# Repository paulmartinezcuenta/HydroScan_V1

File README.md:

<div align="center">

#  Mechatronics & IoT Engineering Projects

*Centralized repository for the development of unified embedded systems.*

</div>

---

> **💡 Manufacturing Note:** To drastically optimize industrial production costs, the PCBs for both projects (HydroScan and AUTOAMBU) have been unified into a single manufacturing panel (Panelized Gerber), sharing the same manufacturing cycle.

---

##  Project 1: HydroScan (Maritime IoT Node)
**Smart buoy for real-time water quality monitoring.***

* 📡 **Telemetry:** Real-time environmental data transmission via LTE networks.
* 📍 **Tracking:** Integrated GPS geolocation for precise positioning of the node.
* 🔋 **Power:** Self-sustaining energy system utilizing solar panels to charge and monitor the sensors autonomously.
* 🔬 **Application:** Oceanographic research and environmental monitoring in coastal areas.
* 📁 [**Explore HydroScan Firmware ➔**](./Firmware_HydroScan)

---

## 🫁 Project 2: AUTOAMBU (Automated Respirator)
**Automated respiratory assistance system.**

* ⚙️ **Actuation & Control:** Precision mechanical control using a DC motor equipped with an encoder and driven by an L298N H-bridge.
* ⚡ **Power Management:** USB Super Fast Charging architecture designed to simultaneously power the circuitry and charge the system.
* 🧠 **Architecture:** Centralized ESP32 32U control logic with dedicated thermal management for continuous and safe operation.
* 📁 [**Explore AUTOAMBU Firmware ➔**](./Firmware_AUTOAMBU)

---

## 👥 Development Team

* ⚡ **Paul** - Hardware Design and PCB Routing 
* 🏗️ **Miguel** - Structural 3D Design
* 💻 **Isaias** - Firmware Development
* 💻 **Alberto** - Firmware Development

---

## 📂 Repository Architecture

| Directory | Description |
| :--- | :--- |
| 🖨️ [**`Hardware_Panelized/`**](./Hardware_Panelized) | Unified KiCad project and joint production Gerber files ready for manufacturing. |
| 💻 [**`Firmware_AUTOAMBU/`**](./Firmware_AUTOAMBU) | Source code (C/C++) and control routines for the medical respirator. |
| 📡 [**`Firmware_HydroScan/`**](./Firmware_HydroScan) | Telemetry logic and sensor reading for the maritime buoy. |
| 📚 [**`Docs/`**](./Docs) | Technical documentation, datasheets, schematics, and 3D models for both systems. |

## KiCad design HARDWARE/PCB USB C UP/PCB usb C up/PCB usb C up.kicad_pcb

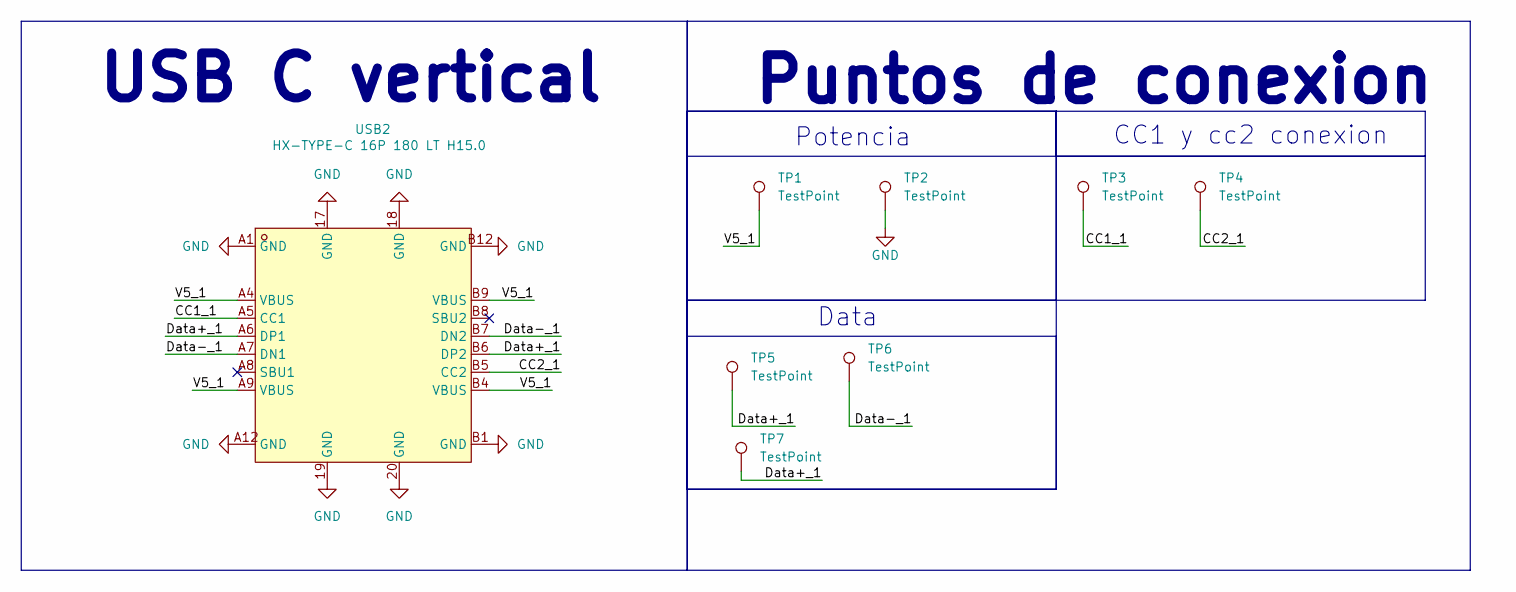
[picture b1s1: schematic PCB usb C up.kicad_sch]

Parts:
TP1, TP2, TP3, TP4, TP5, TP6, TP7: TestPoint; TestPoint_THTPad_2.0x2.0mm_Drill1.0mm
USB2: HX-TYPE-C 16P 180 LT H15.0; USB-C-SMD_HX-TYPE-C-16P-180-LT-H15.0; LCSC Part C49261573

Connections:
/CC1_1: TP3.1 (1_1), USB2.A5 (CC1)
/CC2_1: TP4.1 (1_1), USB2.B5 (CC2)
/Data+_1: TP5.1 (1_1), TP7.1 (1_1), USB2.A6 (DP1), USB2.B6 (DP2)
/Data-_1: TP6.1 (1_1), USB2.A7 (DN1), USB2.B7 (DN2)
/V5_1: TP1.1 (1_1), USB2.A4 (VBUS), USB2.A9 (VBUS), USB2.B4 (VBUS), USB2.B9 (VBUS)
GND: TP2.1 (1_1), USB2.17 (GND), USB2.18 (GND), USB2.19 (GND), USB2.20 (GND), USB2.A1 (GND), USB2.A12 (GND), USB2.B1 (GND), USB2.B12 (GND)

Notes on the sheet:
Potencia
USB C vertical
Data
CC1 y cc2 conexion
Puntos de conexion

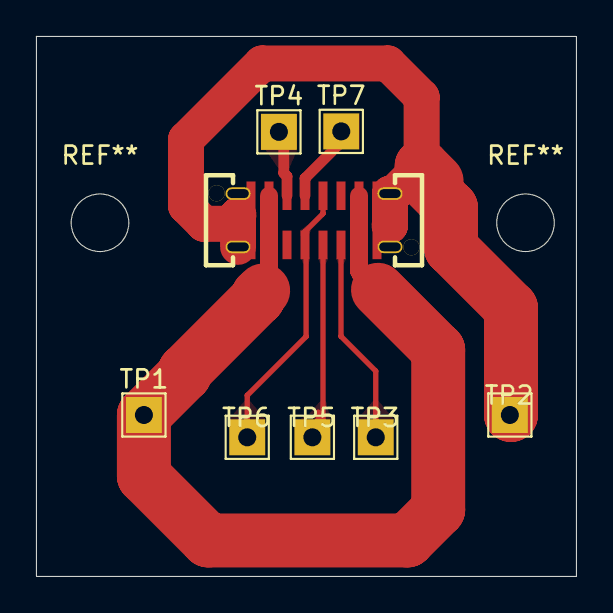
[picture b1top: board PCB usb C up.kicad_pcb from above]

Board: 2 copper layers, 30.0 x 30.0 mm, 8 parts (0 on the bottom side), 6 nets.

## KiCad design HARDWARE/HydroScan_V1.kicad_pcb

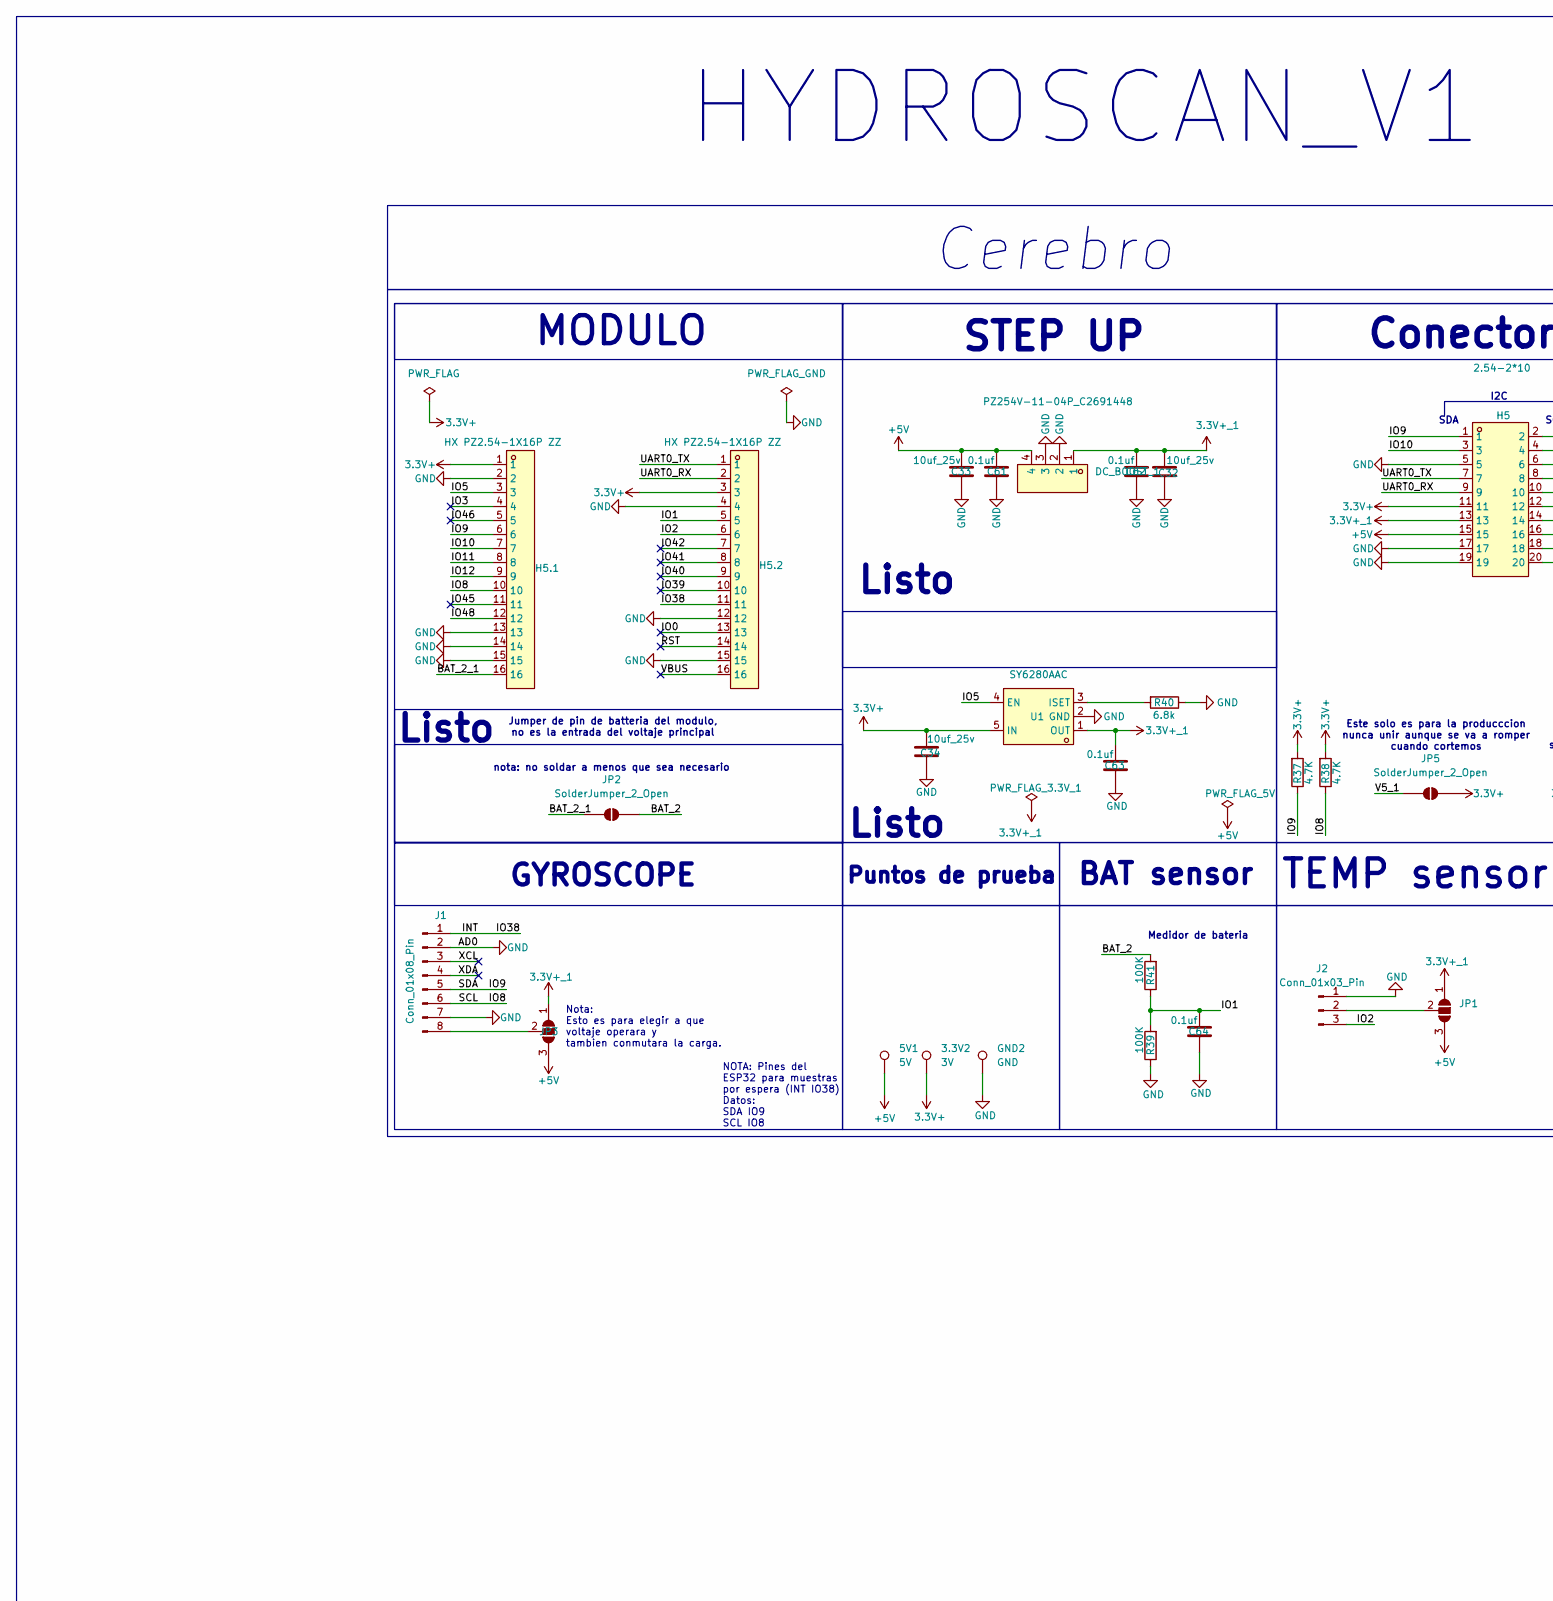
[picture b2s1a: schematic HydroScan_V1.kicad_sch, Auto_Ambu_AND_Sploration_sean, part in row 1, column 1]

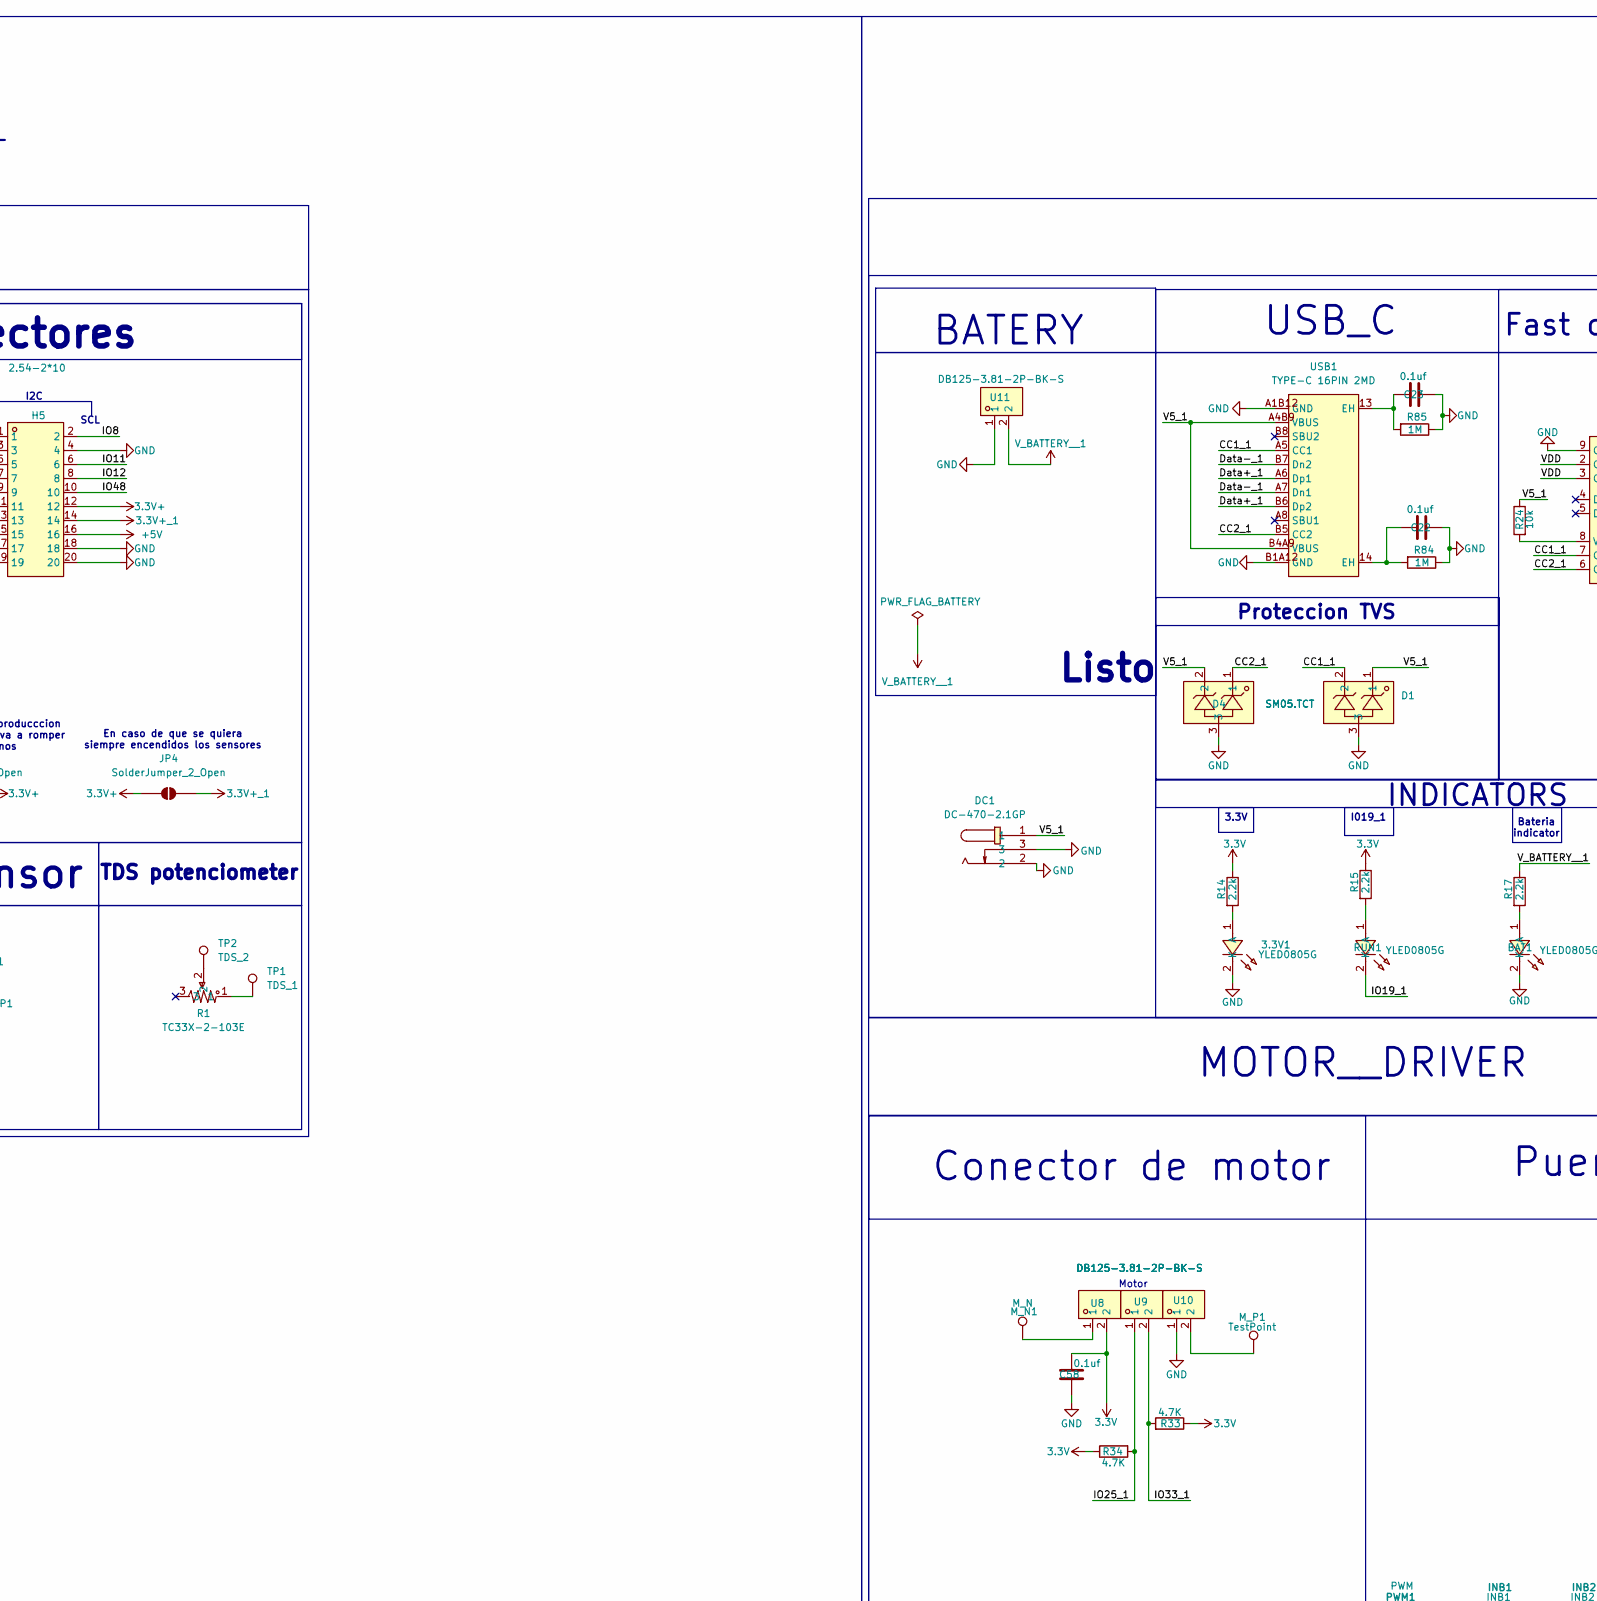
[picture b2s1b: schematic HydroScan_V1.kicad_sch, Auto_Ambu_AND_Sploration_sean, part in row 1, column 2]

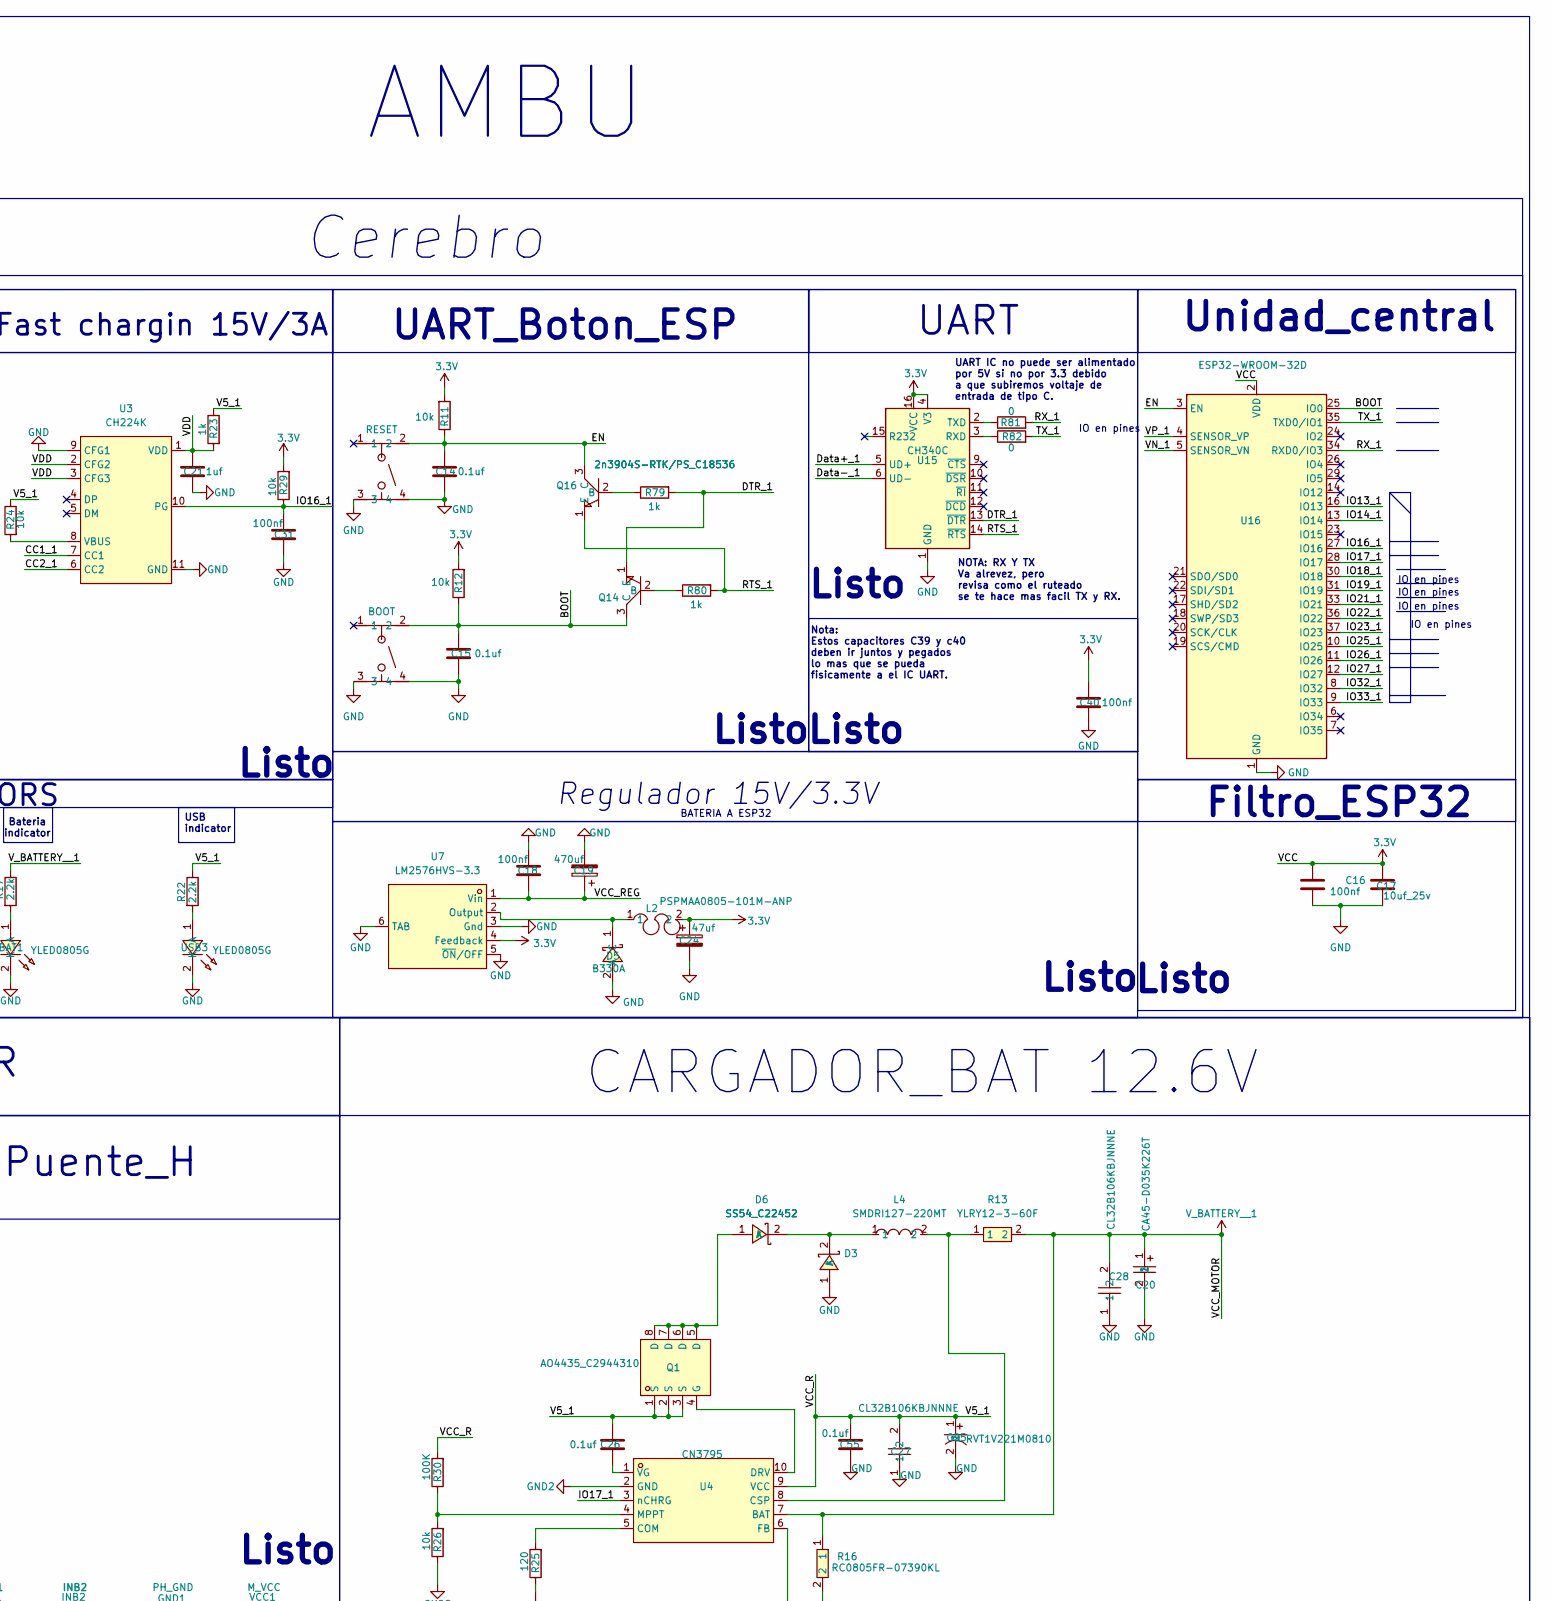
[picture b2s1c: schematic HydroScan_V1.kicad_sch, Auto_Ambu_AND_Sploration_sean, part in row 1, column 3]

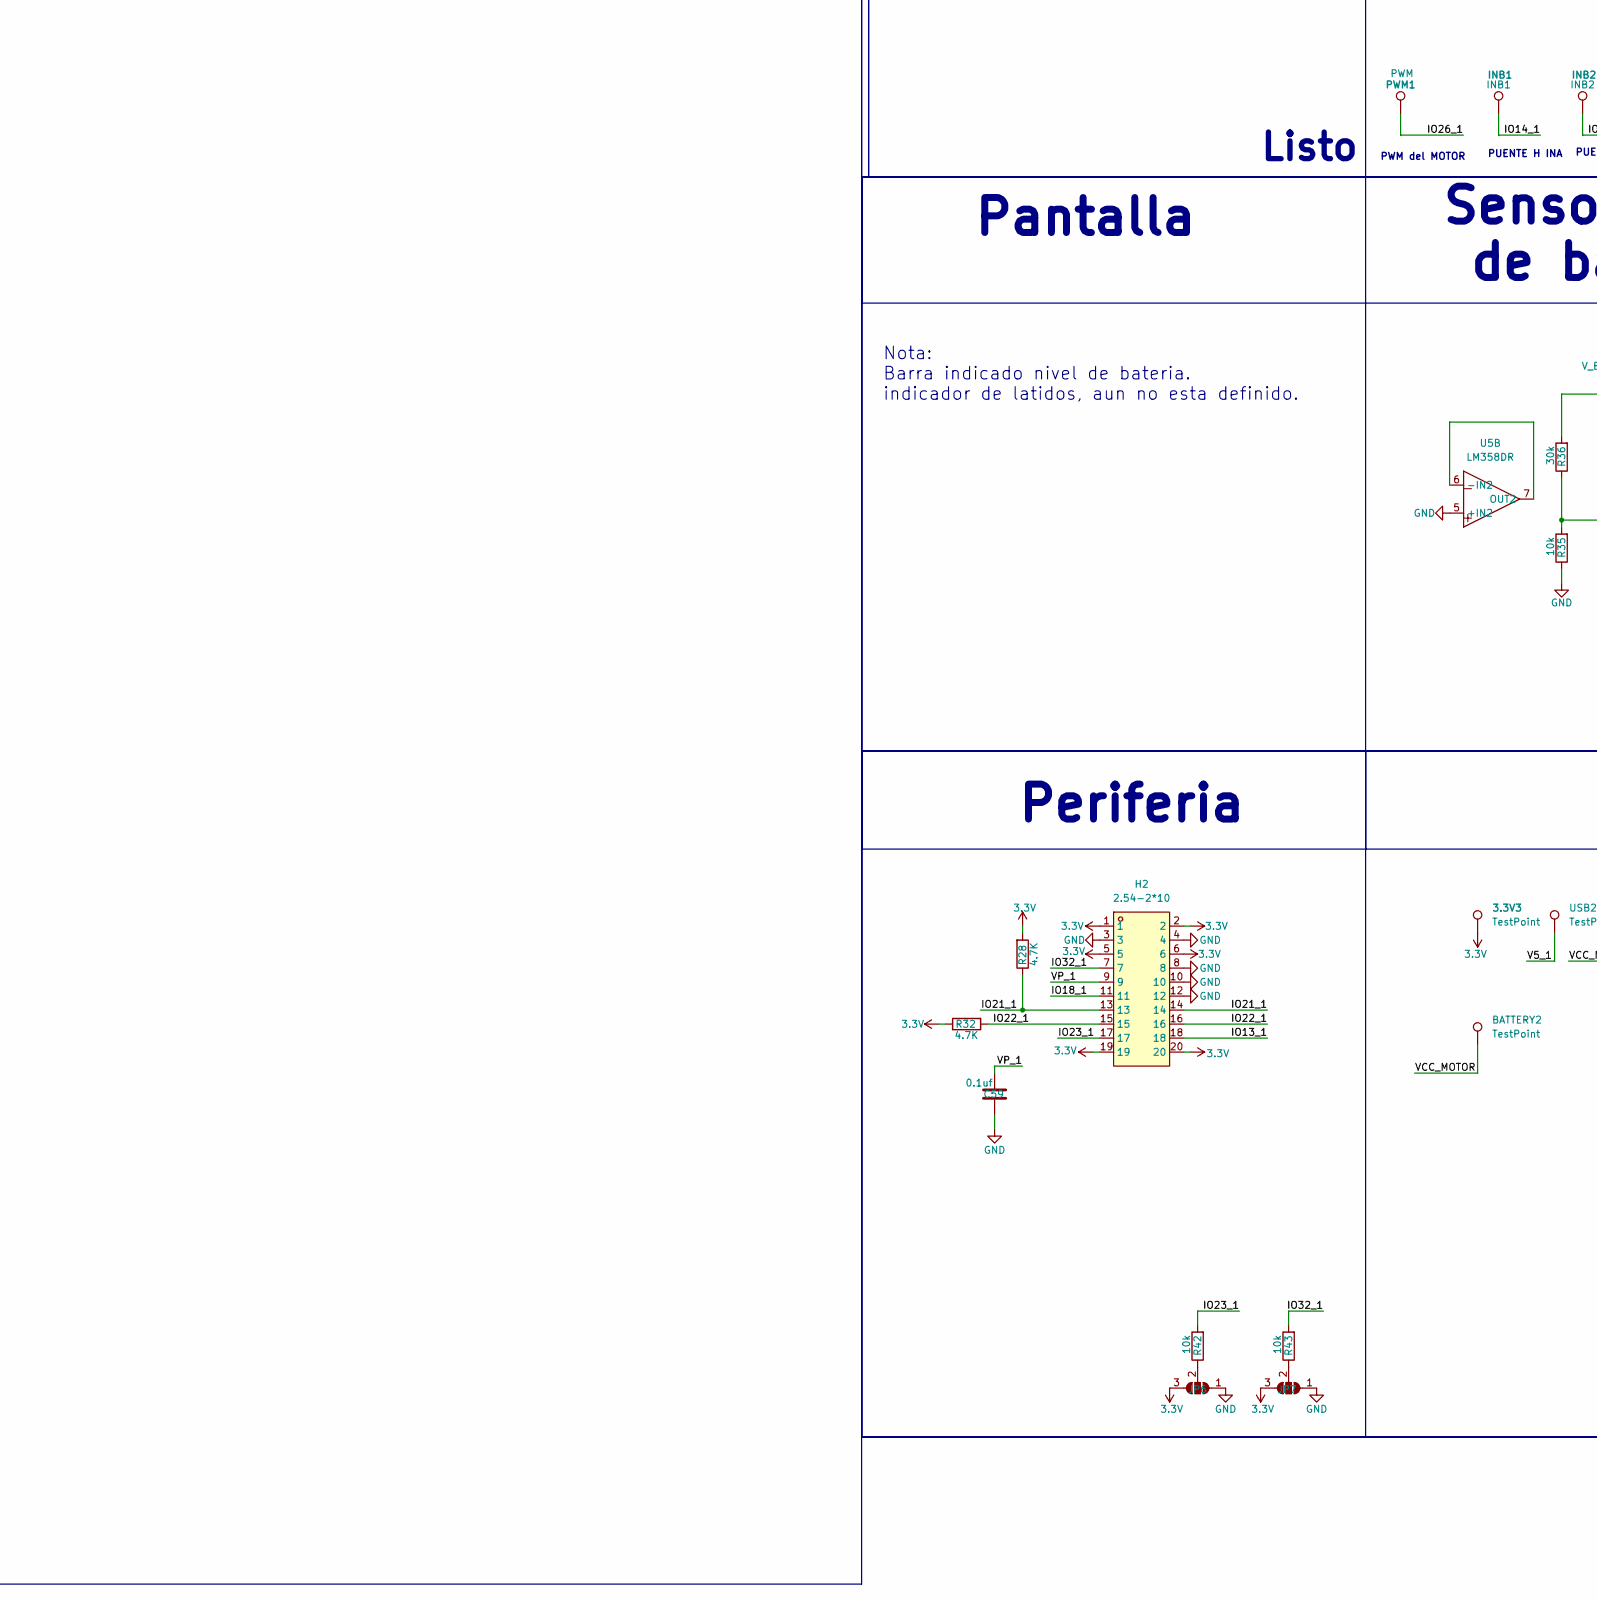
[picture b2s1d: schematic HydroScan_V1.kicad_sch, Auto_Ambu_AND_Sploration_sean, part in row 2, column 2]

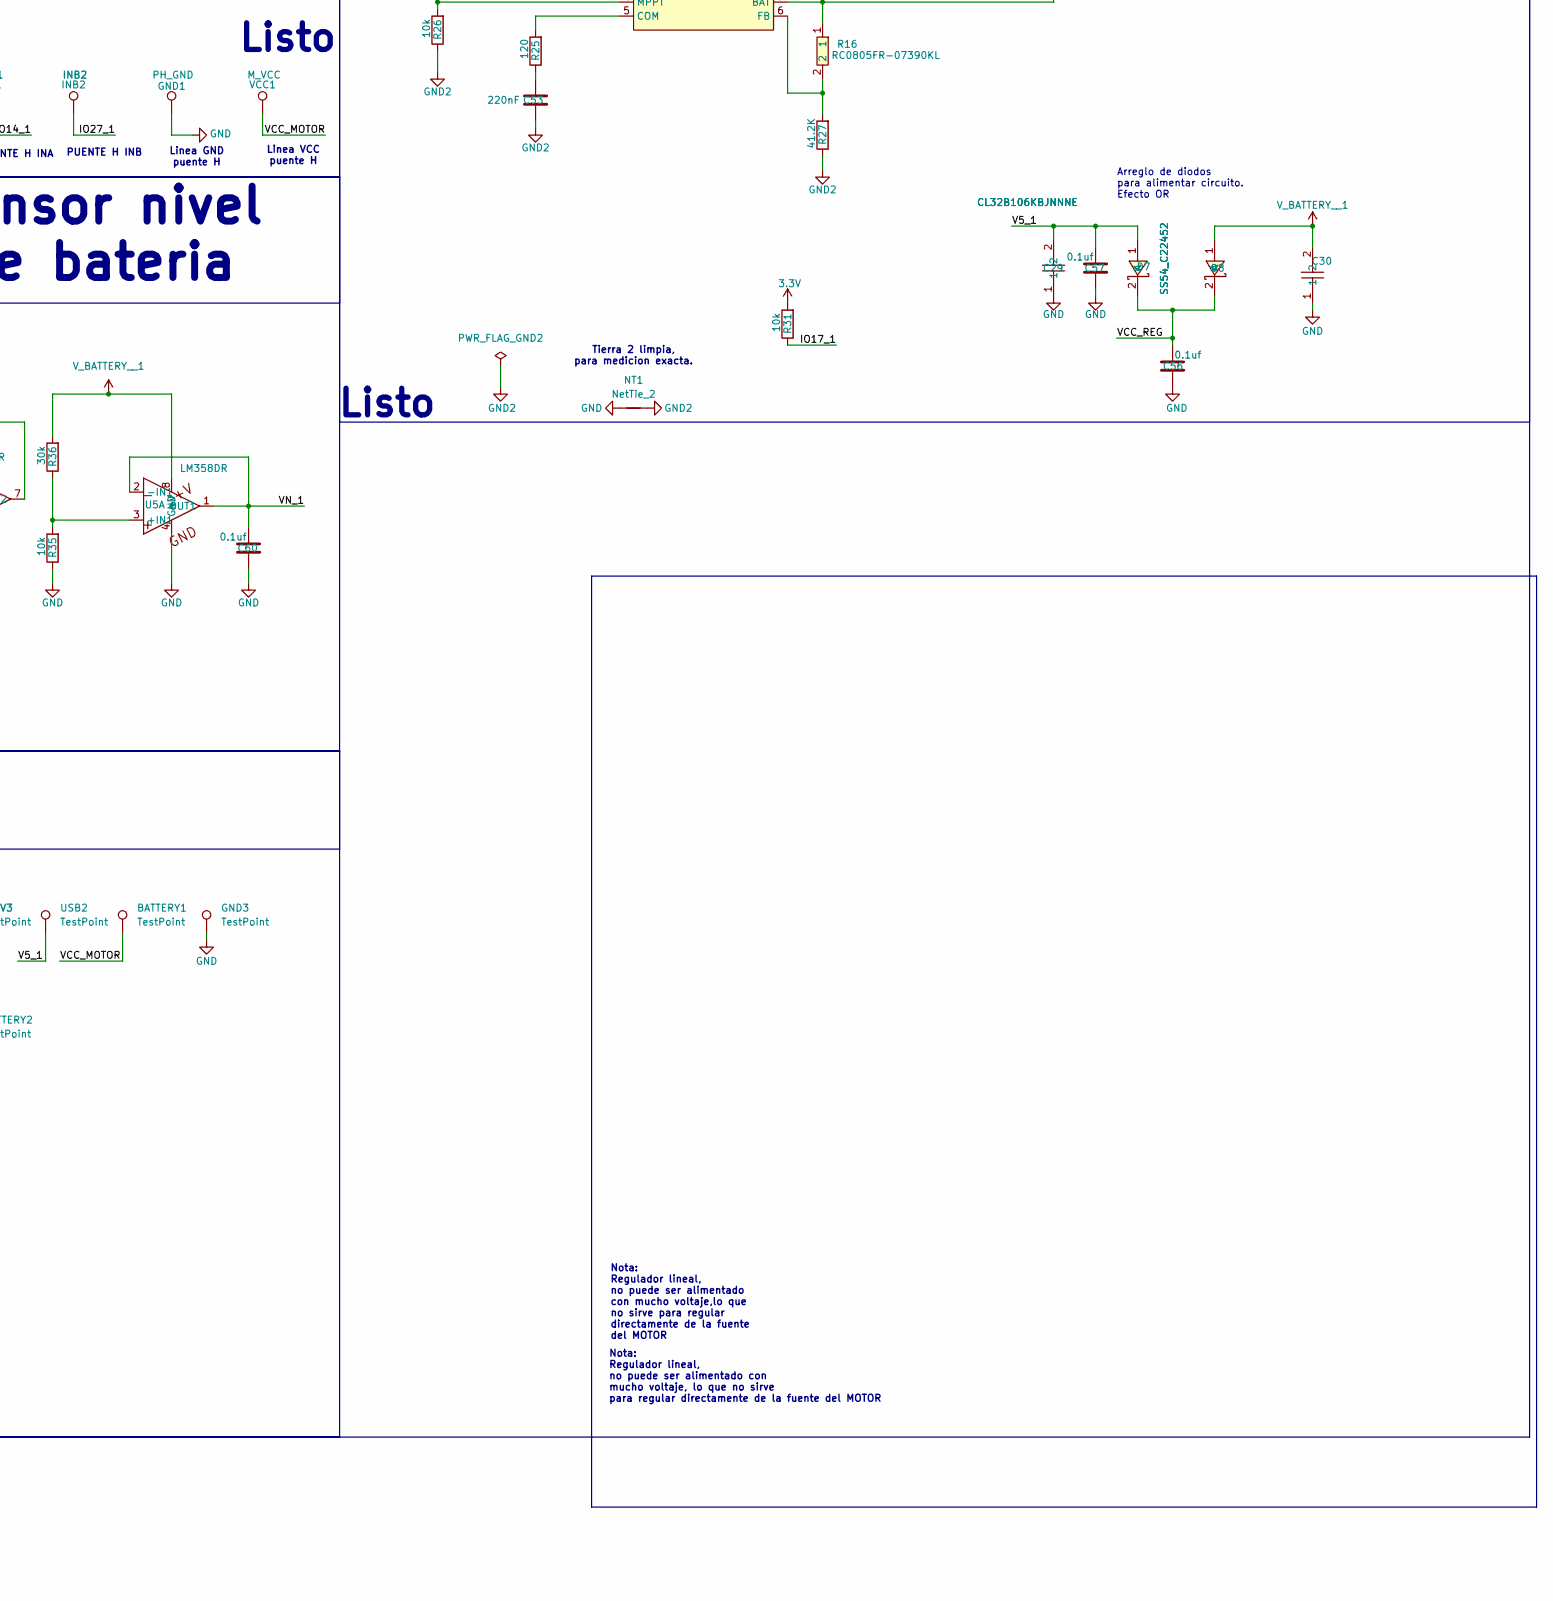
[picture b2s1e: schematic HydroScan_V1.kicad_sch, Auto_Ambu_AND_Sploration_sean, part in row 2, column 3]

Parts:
3.3V1: YLED0805G; LED0805-FD-GREEN; MPN YLED0805G; LCSC Part C25170728
3.3V2: 3V; TestPoint_Pad_2.5x2.5mm
3.3V3: TestPoint; TestPoint_Pad_2.0x2.0mm
5V1: 5V; TestPoint_Pad_2.5x2.5mm
BAT1: YLED0805G; LED0805-FD-GREEN; MPN YLED0805G; LCSC Part C25170728
BATTERY1, BATTERY2: TestPoint; TestPoint_Pad_2.0x2.0mm
C14, C15, C22, C23, C26, C55, C56, C57, C58, C59, C60, C61, C62, C63, C64: 0.1uf; C_0805_2012Metric_Pad1.18x1.45mm_HandSolder
C16, C18, C31, C40: 100nf; C_0805_2012Metric_Pad1.18x1.45mm_HandSolder
C17, C32, C33, C34: 10uf_25v; C_0805_2012Metric_Pad1.18x1.45mm_HandSolder
C19: 470uf; C_Elec_10x10.2; LCSC C72518
C20: CA45-D035K226T; CAP-SMD_L7.3-W4.3-R-RD; MPN CA45-D035K226T; LCSC Part C126947
C21: 1uf; C_0805_2012Metric_Pad1.18x1.45mm_HandSolder
C24: 47uf; C_Elec_6.3x7.7; LCSC C72523
C25: RVT1V221M0810; CAP-SMD_BD8.0-L8.3-W8.3-LS9.1-FD; MPN RVT1V221M0810; LCSC Part C3340
C27, C28, C29, C30: CL32B106KBJNNNE; C1210; MPN CL32B106KBJNNNE; LCSC Part C138687
C53: 220nF; C_0805_2012Metric_Pad1.18x1.45mm_HandSolder
D1, D4: SM05.TCT; SOT-23-3_L2.9-W1.3-P0.95-LS2.4-BR; MPN SM05.TCT; LCSC Part C85197
D3, D6, D7, D8: SS54_C22452; SMA_L4.4-W2.8-LS5.4-R-RD; MPN SS54; LCSC Part C22452
D5: B330A; SMA_L4.3-W2.6-LS5.1-RD; MPN B330A; LCSC Part C52037930
DC1: DC-470-2.1GP; DC-IN-TH_DC-470-2.1GP; MPN DC-470-2.1GP; LCSC Part C194407
DC_BOOST_1: PZ254V-11-04P_C2691448; HDR-TH_4P-P2.54-V-M; MPN PZ254V-11-04P; LCSC Part C2691448
GND1: PH_GND; PinHeader_1x01_P2.00mm_Vertical
GND2: GND; TestPoint_Pad_2.5x2.5mm
GND3: TestPoint; TestPoint_Pad_2.0x2.0mm
H2, H5: 2.54-2*10; HDR-TH_20P-P2.54-V-M-R2-C10-S2.54; MPN 2.54-2*10; LCSC Part C5116480
H5.1, H5.2: HX PZ2.54-1X16P ZZ; HDR-TH_16P-P2.54-V-M_2; MPN HX PZ2.54-1x16P ZZ; LCSC Part C42372508
INB1: INB1; PinHeader_1x01_P2.00mm_Vertical
INB2: INB2; PinHeader_1x01_P2.00mm_Vertical
J1: Conn_01x08_Pin; MPU6050_Module
J2: Conn_01x03_Pin; PinHeader_1x03_P2.54mm_Vertical
JP1, JP3, JP6, JP7: SolderJumper_3_Open; SolderJumper-3_P1.3mm_Open_RoundedPad1.0x1.5mm_NumberLabels
JP2, JP4, JP5: SolderJumper_2_Open; SolderJumper-2_P1.3mm_Open_Pad1.0x1.5mm
L2: PSPMAA0805-101M-ANP; IND-SMD_L8.5-W8.0_PCC-M0854M; LCSC Part C2962892
L4: SMDRI127-220MT; IND-SMD_L12.3-W12.3_SMDRI127; MPN SMDRI127-220MT; LCSC Part C9905
M_N1: M_N; PinHeader_1x01_P2.00mm_Vertical
M_P1: TestPoint; PinHeader_1x01_P2.00mm_Vertical
NT1: NetTie_2; NetTie-2_SMD_Pad0.5mm
PWM1: PWM; PinHeader_1x01_P2.00mm_Vertical
Q1: AO4435_C2944310; SOP-8_L5.0-W3.8-P1.27-LS6.0-BL; MPN AO4435; LCSC Part C2944310
Q14, Q16: 2n3904S-RTK/PS_C18536; SOT-23-3_L2.9-W1.3-P1.90-LS2.4-TR; LCSC Part C18536
R1: TC33X-2-103E; RES-ADJ-SMD_3P-L3.0-W3.8-P1.75-BR; MPN TC33X-2-103E; LCSC Part C719176
R11, R12, R26, R29, R31, R35, R42, R43: 10k; R_0805_2012Metric_Pad1.20x1.40mm_HandSolder
R13: YLRY12-3-60F; R2512; MPN YLRY12-3-60F; LCSC Part C22468068
R14, R15, R17, R22: 2.2k; R_0805_2012Metric_Pad1.20x1.40mm_HandSolder
R16: RC0805FR-07390KL; R0805; MPN RC0805FR-07390KL; LCSC Part C137535
R23, R79, R80: 1k; R_0805_2012Metric_Pad1.20x1.40mm_HandSolder
R24: 10k; C_0805_2012Metric_Pad1.18x1.45mm_HandSolder
R25: 120; R_0805_2012Metric_Pad1.20x1.40mm_HandSolder
R27: 41.2K; R_0805_2012Metric_Pad1.20x1.40mm_HandSolder; LCSC C2077335
R28, R32, R33, R34, R37, R38: 4.7K; R_0805_2012Metric_Pad1.20x1.40mm_HandSolder
R30, R39, R41: 100K; R_0805_2012Metric_Pad1.20x1.40mm_HandSolder
R36: 30k; R_0805_2012Metric_Pad1.20x1.40mm_HandSolder
R40: 6.8k; R_0805_2012Metric_Pad1.20x1.40mm_HandSolder
R81, R82: 0; R_0805_2012Metric_Pad1.20x1.40mm_HandSolder
R84, R85: 1M; R_0805_2012Metric_Pad1.20x1.40mm_HandSolder
RUN1: YLED0805G; LED0805-FD-GREEN; MPN YLED0805G; LCSC Part C25170728
SW2: BOOT; SW-SMD_4P-L6.0-W6.0-P4.50-LS8.2; LCSC Part C7528752
SW4: RESET; SW-SMD_4P-L6.0-W6.0-P4.50-LS8.2; LCSC Part C7528752
TP1: TDS_1; TestPoint_THTPad_D4.0mm_Drill2.0mm
TP2: TDS_2; TestPoint_THTPad_D4.0mm_Drill2.0mm
U1: SY6280AAC; SOT-23-5_L3.0-W1.7-P0.95-LS2.8-BL; MPN SY6280AAC; LCSC Part C55136
U3: CH224K; ESSOP-10_L4.9-W3.9-P1.0-LS6.0-TL-EP; MPN CH224K; LCSC Part C970725
U4: CN3795; SSOP-10_L4.9-W3.9-P1.00-LS6.0-BL; MPN CN3795; LCSC Part C150555
U5: LM358DR; SOIC-8_L5.0-W4.0-P1.27-LS6.0-BL; MPN LM358DR; LCSC Part C5423
U7: LM2576HVS-3.3; PG-TO-263-5_L10.2-W8.7-P1.70-LS14.4-BR; LCSC Part C347436
U8, U9, U10, U11: DB125-3.81-2P-BK-S; CONN-TH_2P-P3.81_DB125-3.81-2P-BK-S; MPN DB125-3.81-2P-BK-S; LCSC Part C430618
U15: CH340C; SOIC-16_3.9x9.9mm_P1.27mm
U16: ESP32-WROOM-32D; ESP32-WROOM-32U
USB1: TYPE-C 16PIN 2MD; USB-C-SMD_TYPE-C-16PIN-2MD-073; MPN TYPE-C 16PIN 2MD(073); LCSC Part C2765186
USB2: TestPoint; TestPoint_Pad_2.0x2.0mm
USB3: YLED0805G; LED0805-FD-GREEN; MPN YLED0805G; LCSC Part C25170728
VCC1: M_VCC; PinHeader_1x01_P2.00mm_Vertical

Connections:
3.3V: 3.3V3.1 (1_1), C16.1, C17.1, C24.1, C40.1, C58.2, H2.1, H2.2, H2.5, H2.6, H2.19, H2.20, JP6.3 (B), JP7.3 (B), L2.2, R11.2, R12.2, R14.1, R15.1, R28.2, R29.2, R31.2, R32.1, R33.1, R34.1, U7.4 (Feedback), U8.2, U15.4 (V3), U15.16 (VCC), U16.2 (VDD)
3.3V+: 3.3V2.1 (1_1), C34.1, H5.11, H5.12, H5.1.1, H5.2.3, JP4.1 (A), JP5.2 (B), R37.2, R38.2, U1.5 (IN)
3.3V+_1: C32.1, C62.2, C63.2, DC_BOOST_1.1, H5.13, H5.14, JP1.1 (A), JP3.1 (A), JP4.2 (B), U1.1 (OUT)
+5V: 5V1.1 (1_1), C33.1, C61.2, DC_BOOST_1.4, H5.15, H5.16, JP1.3 (B), JP3.3 (B)
/BAT_2: JP2.2 (B), R41.2
/BAT_2_1: H5.1.16, JP2.1 (A)
/BOOT: C15.1, Q14.3 (C), R12.1, SW2.2, U16.25 (IO0)
/CC1_1: D1.2, U3.7 (CC1), USB1.A5 (CC1)
/CC2_1: D4.1, U3.6 (CC2), USB1.B5 (CC2)
/DTR_1: Q14.1 (E), R79.2, U15.13 (~DTR)
/Data+_1: U15.5 (UD+), USB1.A6 (Dp1), USB1.B6 (Dp2)
/Data-_1: U15.6 (UD-), USB1.A7 (Dn1), USB1.B7 (Dn2)
/EN: C14.1, Q16.3 (C), R11.1, SW4.2, U16.3 (EN)
/INT: H5.2.11, J1.1
/IO0: H5.2.13
/IO1: C64.2, H5.2.5, R39.2, R41.1
/IO2: H5.2.6, J2.3
/IO3: H5.1.4
/IO5: H5.1.3, U1.4 (EN)
/IO8: H5.2, H5.1.10, J1.6, R38.1
/IO9: H5.1, H5.1.6, J1.5, R37.1
/IO10: H5.3, H5.1.7
/IO11: H5.6, H5.1.8
/IO12: H5.8, H5.1.9
/IO13_1: H2.18, U16.16 (IO13)
/IO14_1: INB1.1 (1_1), U16.13 (IO14)
/IO16_1: C31.2, R29.1, U3.10 (PG), U16.27 (IO16)
/IO17_1: R31.1, U4.3 (nCHRG), U16.28 (IO17)
/IO18_1: H2.11, U16.30 (IO18)
/IO19_1: RUN1.2 (K), U16.31 (IO19)
/IO21_1: H2.13, H2.14, R28.1, U16.33 (IO21)
/IO22_1: H2.15, H2.16, R32.2, U16.36 (IO22)
/IO23_1: H2.17, R42.2, U16.37 (IO23)
/IO25_1: R34.2, U9.1, U16.10 (IO25)
/IO26_1: PWM1.1 (1_1), U16.11 (IO26)
/IO27_1: INB2.1 (1_1), U16.12 (IO27)
/IO32_1: H2.7, R43.2, U16.8 (IO32)
/IO33_1: R33.2, U9.2, U16.9 (IO33)
/IO39: H5.2.10
/IO40: H5.2.9
/IO41: H5.2.8
/IO42: H5.2.7
/IO45: H5.1.11
/IO46: H5.1.5
/IO48: H5.10, H5.1.12
/RST: H5.2.14
/RTS_1: Q16.1 (E), R80.2, U15.14 (~RTS)
/RX_1: R81.2, U16.34 (RXD0/IO3)
/TX_1: R82.2, U16.35 (TXD0/IO1)
/UART0_RX: H5.9, H5.2.2
/UART0_TX: H5.7, H5.2.1
/V5_1: C25.1, C26.2, C27.2, C29.2, C55.2, C57.2, D1.1, D4.2, D7.1 (A), DC1.1, JP5.1 (A), Q1.1 (S), Q1.2 (S), Q1.3 (S), R22.1, R23.1, R24.1, R30.2, U4.9 (VCC), USB1.A4B9 (VBUS), USB1.B4A9 (VBUS), USB2.1 (1_1)
/VBUS: H5.2.16
/VCC_REG: C18.1, C19.1, C56.2, D7.2 (K), D8.2 (K), U7.1 (Vin)
/VDD: C21.1, R23.2, U3.1 (VDD), U3.2 (CFG2), U3.3 (CFG3)
/VN_1: C60.2, U5.1 (OUT1), U5.2 (-IN1), U16.5 (SENSOR_VN)
/VP_1: C59.2, H2.9, U16.4 (SENSOR_VP)
/XCL: J1.3
/XDA: J1.4
GND: 3.3V1.2 (K), BAT1.2 (K), C14.2, C15.2, C16.2, C17.2, C18.2, C19.2, C20.2, C21.2, C22.2, C23.2, C24.2, C25.2, C27.1, C28.1, C29.1, C30.1, C31.1, C32.2, C33.2, C34.2, C40.2, C55.1, C56.1, C57.1, C58.1, C59.1, C60.1, C61.1, C62.1, C63.1, C64.1, D1.3, D3.1 (A), D4.3, D5.2 (A), DC1.2, DC1.3, DC_BOOST_1.2, DC_BOOST_1.3, GND1.1 (1_1), GND2.1 (1_1), GND3.1 (1_1), H2.3, H2.4, H2.8, H2.10, H2.12, H5.4, H5.5, H5.17, H5.18, H5.19, H5.20, H5.1.2, H5.1.13, H5.1.14, H5.1.15, H5.2.4, H5.2.12, H5.2.15, J1.2, J1.7, J2.1, JP6.1 (A), JP7.1 (A), NT1.1, R35.1, R39.1, R40.1, R84.1, R85.1, SW2.3, SW2.4, SW4.3, SW4.4, U1.2 (GND), U3.9 (CFG1), U3.11 (GND), U5.4 (GND), U5.5 (+IN2), U7.3 (Gnd), U7.5 (~ON/OFF), U7.6 (TAB), U10.1, U11.1, U15.1 (GND), U16.1 (GND), U16.15 (GND), U16.38 (GND), U16.39 (GND), USB1.A1B12 (GND), USB1.B1A12 (GND), USB3.2 (K); also elsewhere on the board
GND2: C53.1, NT1.2, R26.1, R27.1, U4.2 (GND)
unnamed: 3.3V1.1 (A), R14.2
unnamed: BAT1.1 (A), R17.2
unnamed: C22.1, R84.2, USB1.14 (EH)
unnamed: C23.1, R85.2, USB1.13 (EH)
unnamed: C53.2, R25.1
unnamed: D3.2 (K), D6.2 (K), L4.1
unnamed: D5.1 (C), L2.1, U7.2 (Output)
unnamed: D6.1 (A), Q1.5 (D), Q1.6 (D), Q1.7 (D), Q1.8 (D)
unnamed: J1.8, JP3.2 (C)
unnamed: J2.2, JP1.2 (C)
unnamed: JP6.2 (C), R42.1
unnamed: JP7.2 (C), R43.1
unnamed: M_N1.1 (1_1), U8.1
unnamed: M_P1.1 (1_1), U10.2
unnamed: Q1.4 (G), U4.10 (DRV)
unnamed: Q14.2 (B), R80.1
unnamed: Q16.2 (B), R79.1
unnamed: R1.1, TP1.1 (1_1)
unnamed: R1.2, TP2.1 (1_1)
unnamed: R15.2, RUN1.1 (A)
unnamed: R40.2, U1.3 (ISET)
unnamed: R24.2, U3.8 (VBUS)
unnamed: R25.2, U4.5 (COM)
unnamed: L4.2, R13.1, U4.8 (CSP)
unnamed: R16.2, R27.2, U4.6 (FB)
unnamed: R26.2, R30.1, U4.4 (MPPT)
unnamed: C26.1, U4.1 (VG)
unnamed: R35.2, R36.1, U5.3 (+IN1)
unnamed: U5.6 (-IN2), U5.7 (OUT2)
unnamed: R82.1, U15.3 (RXD)
unnamed: R81.1, U15.2 (TXD)
unnamed: R22.2, USB3.1 (A)
V_BATTERY__1: BATTERY1.1 (1_1), BATTERY2.1 (1_1), C20.1, C28.2, C30.2, D8.1 (A), R13.2, R16.1, R17.1, R36.2, U4.7 (BAT), U5.8 (+V), U11.2, VCC1.1 (1_1)

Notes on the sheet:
Periferia
MOTOR__DRIVER
NOTA: RX Y TX Va alrevez, pero revisa como el ruteado se te hace mas facil TX y RX.
IO en pines
Jumper de pin de batteria del modulo, no es la entrada del voltaje principal
Unidad_central
BATERY
Nota: Esto es para elegir a que voltaje operara y tambien conmutara la carga.
NOTA: Pines del ESP32 para muestras por espera (INT IO38) Datos: SDA IO9 SCL IO8
HYDROSCAN_V1
Linea GND puente H
Este solo es para la producccion nunca unir aunque se va a romper cuando cortemos
Nota: Regulador lineal, no puede ser alimentado con mucho voltaje, lo que no sirve para regular directamente de la fuente del MOTOR
Listo
Linea VCC puente H
Nota: Barra indicado nivel de bateria. indicador de latidos, aun no esta definido.
SCL
PWM del MOTOR
UART
Nota: Estos capacitores C39 y c40 deben ir juntos y pegados lo mas que se pueda fisicamente a el IC UART.
Fast chargin 15V/3A
STEP UP
Cerebro
Conectores
Puntos de prueba
PUENTE H INB
Nota: Regulador lineal, no puede ser alimentado con mucho voltaje,lo que no sirve para regular directamente de la fuente del MOTOR
nota: no soldar a menos que sea necesario
USB_C
Sensor nivel de bateria
CARGADOR_BAT 12.6V
I2C
Arreglo de diodos para alimentar circuito. Efecto OR
Filtro_ESP32
En caso de que se quiera siempre encendidos los sensores
Medidor de bateria
Pantalla
PUENTE H INA
BAT sensor
Motor
